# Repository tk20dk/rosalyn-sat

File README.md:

# rosalyn-sat
Rosalyn LoRa satellite receiver

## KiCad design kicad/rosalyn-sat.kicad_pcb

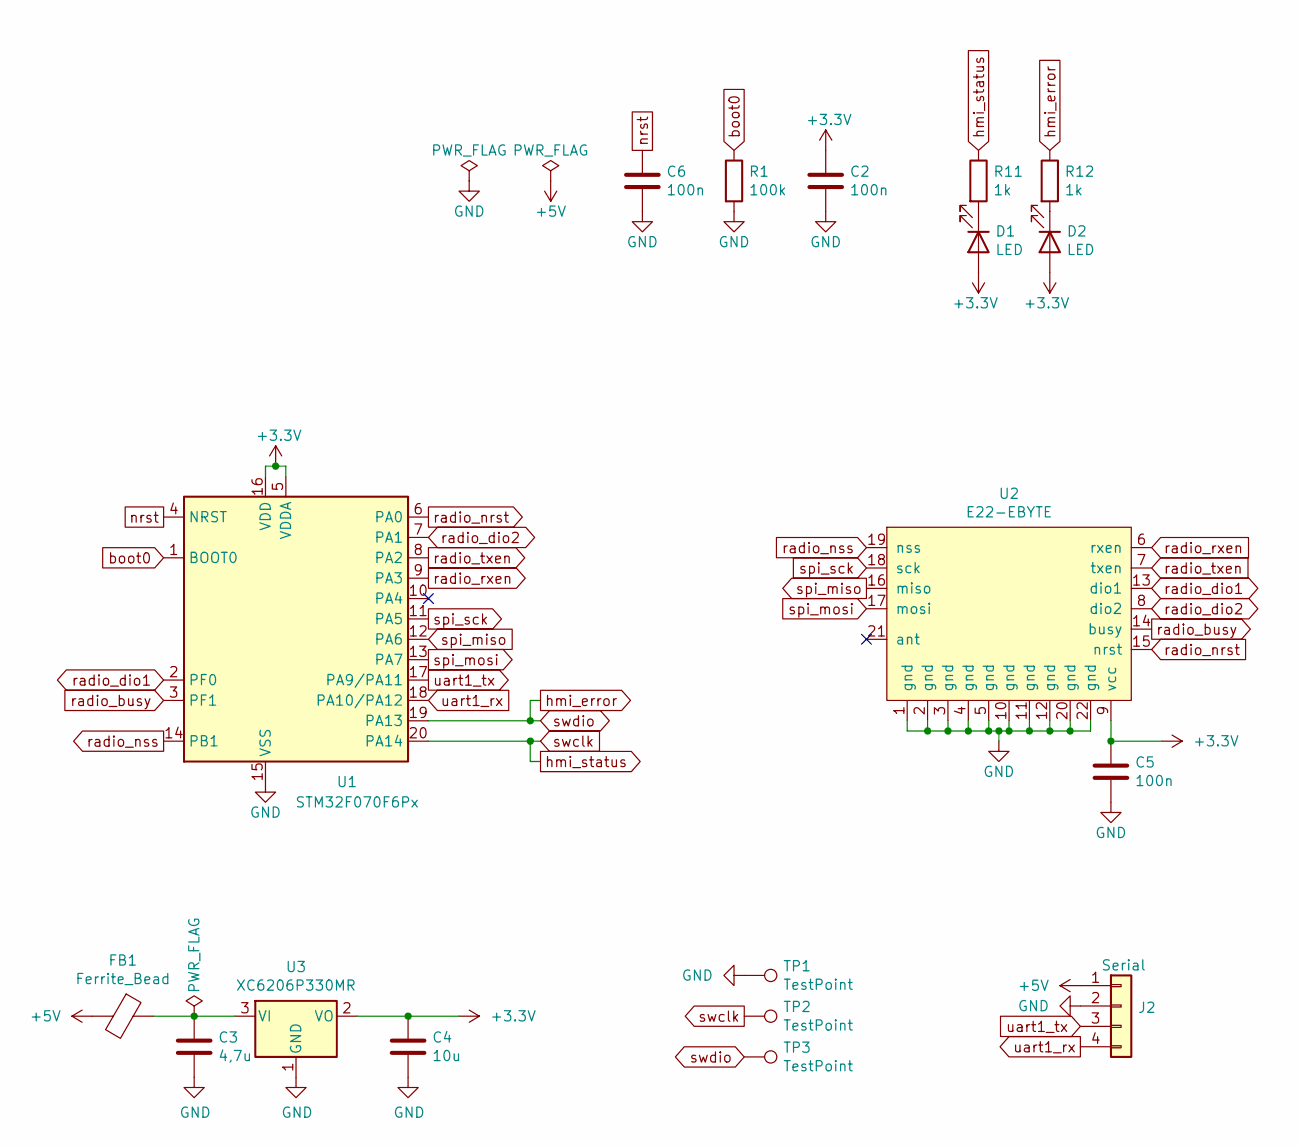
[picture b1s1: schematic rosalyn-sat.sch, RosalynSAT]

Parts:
C2, C5, C6: 100n; C_0603_1608Metric
C3: 4,7u; C_0805_2012Metric
C4: 10u; C_0805_2012Metric
D1, D2: LED; LED_0603_1608Metric
FB1: Ferrite_Bead; L_0805_2012Metric
J2: Serial; JST_SH_SM04B-SRSS-TB_1x04-1MP_P1.00mm_Horizontal
R1: 100k; R_0603_1608Metric
R11, R12: 1k; R_0603_1608Metric
TP1, TP2, TP3: TestPoint; TestPoint_Pad_1.0x1.0mm
U1: STM32F070F6Px; TSSOP-20_4.4x6.5mm_P0.65mm
U2: E22-EBYTE
U3: XC6206P330MR; SOT-23

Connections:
+3V3: C2.1, C4.1, C5.1, D1.2 (A), D2.2 (A), U1.5 (VDDA), U1.16 (VDD), U2.9 (vcc), U3.2 (VO)
+5V: FB1.2, J2.1
GND: C2.2, C3.2, C4.2, C5.2, C6.2, J2.2, R1.2, TP1.1, U1.15 (VSS), U2.1 (gnd), U2.2 (gnd), U2.3 (gnd), U2.4 (gnd), U2.5 (gnd), U2.10 (gnd), U2.11 (gnd), U2.12 (gnd), U2.20 (gnd), U2.22 (gnd), U3.1 (GND)
unnamed: C3.1, FB1.1, U3.3 (VI)
unnamed: D1.1 (K), R11.2
unnamed: D2.1 (K), R12.2
boot0: R1.1, U1.1 (BOOT0)
hmi_error: R12.1, TP3.1, U1.19 (PA13)
hmi_status: R11.1, TP2.1, U1.20 (PA14)
nrst: C6.1, U1.4 (NRST)
radio_busy: U1.3 (PF1), U2.14 (busy)
radio_dio1: U1.2 (PF0), U2.13 (dio1)
radio_dio2: U1.7 (PA1), U2.8 (dio2)
radio_nrst: U1.6 (PA0), U2.15 (nrst)
radio_nss: U1.14 (PB1), U2.19 (nss)
radio_rxen: U1.9 (PA3), U2.6 (rxen)
radio_txen: U1.8 (PA2), U2.7 (txen)
spi_miso: U1.12 (PA6), U2.16 (miso)
spi_mosi: U1.13 (PA7), U2.17 (mosi)
spi_sck: U1.11 (PA5), U2.18 (sck)
uart1_rx: J2.4, U1.18 (PA10/PA12)
uart1_tx: J2.3, U1.17 (PA9/PA11)

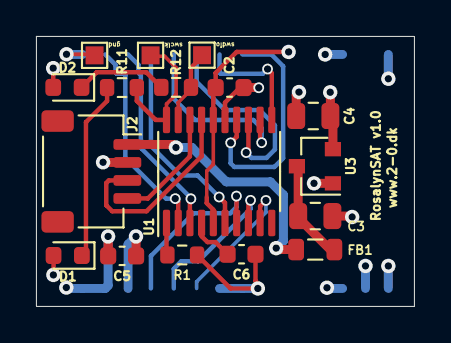
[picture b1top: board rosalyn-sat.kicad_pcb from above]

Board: 4 copper layers, 21.0 x 15.0 mm, 18 parts (1 on the bottom side), 22 nets.

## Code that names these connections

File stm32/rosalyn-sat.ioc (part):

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Mcu.Name=STM32F042F6Px
Mcu.Package=TSSOP20
Mcu.UserName=STM32F042F6Px
PA0.GPIOParameters=PinState,GPIO_Label
PA0.GPIO_Label=RADIO_NRST
PA0.PinState=GPIO_PIN_SET
PA0.Signal=GPIO_Output
PA1.GPIOParameters=GPIO_Label
PA1.GPIO_Label=RADIO_DIO2
PA1.Signal=GPIO_Input
PA10.GPIOParameters=GPIO_PuPd
PA10.GPIO_PuPd=GPIO_PULLUP
PA10.Mode=Asynchronous
PA10.Signal=USART1_RX
PA13.GPIOParameters=GPIO_Label
PA13.GPIO_Label=HMI_ERROR
PA13.Mode=Serial_Wire
PA13.Signal=SYS_SWDIO
PA14.GPIOParameters=GPIO_Label
PA14.GPIO_Label=HMI_STATUS
PA14.Mode=Serial_Wire
PA14.Signal=SYS_SWCLK
PA2.GPIOParameters=PinState,GPIO_Label
PA2.GPIO_Label=RADIO_TXEN
PA2.PinState=GPIO_PIN_RESET
PA2.Signal=GPIO_Output
PA3.GPIOParameters=PinState,GPIO_Label
PA3.GPIO_Label=RADIO_RXEN
PA3.PinState=GPIO_PIN_RESET
PA3.Signal=GPIO_Output
PA5.Mode=Full_Duplex_Master
PA5.Signal=SPI1_SCK
PA6.GPIOParameters=GPIO_PuPd
PA6.GPIO_PuPd=GPIO_PULLUP
PA6.Mode=Full_Duplex_Master
PA6.Signal=SPI1_MISO
PA7.Mode=Full_Duplex_Master
PA7.Signal=SPI1_MOSI
PA9.Mode=Asynchronous
PA9.Signal=USART1_TX
PB1.GPIOParameters=PinState,GPIO_Label
PB1.GPIO_Label=RADIO_NSS
PB1.PinState=GPIO_PIN_SET
PB1.Signal=GPIO_Output
PF0-OSC_IN.GPIOParameters=GPIO_PuPd,GPIO_Label
PF0-OSC_IN.GPIO_Label=RADIO_DIO1
PF0-OSC_IN.GPIO_PuPd=GPIO_NOPULL
PF0-OSC_IN.Signal=GPXTI0
PF1-OSC_OUT.GPIOParameters=GPIO_PuPd,GPIO_Label
PF1-OSC_OUT.GPIO_Label=RADIO_BUSY
PF1-OSC_OUT.GPIO_PuPd=GPIO_NOPULL
PF1-OSC_OUT.Signal=GPIO_Input
RCC.SYSCLKFreq_VALUE=48000000
RCC.SYSCLKSource=RCC_SYSCLKSOURCE_HSI48
board=custom

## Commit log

2020-11-19 created initial kicad and stm32 projects
2020-11-23 rosalyn-sat_v1.0
2020-11-26 Tage (#2)
    * rosalyn-sat_v1.0
    * added nvdata driver
    * removed kicad bak files
    * removed stm32__ folder
2020-12-09 support for v1.00 hardware
2020-12-15 enabled TXCO to remove startup delay
